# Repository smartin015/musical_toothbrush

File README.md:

```
python3 send_tones.py africa_solo_1pt.mid 1.5
```

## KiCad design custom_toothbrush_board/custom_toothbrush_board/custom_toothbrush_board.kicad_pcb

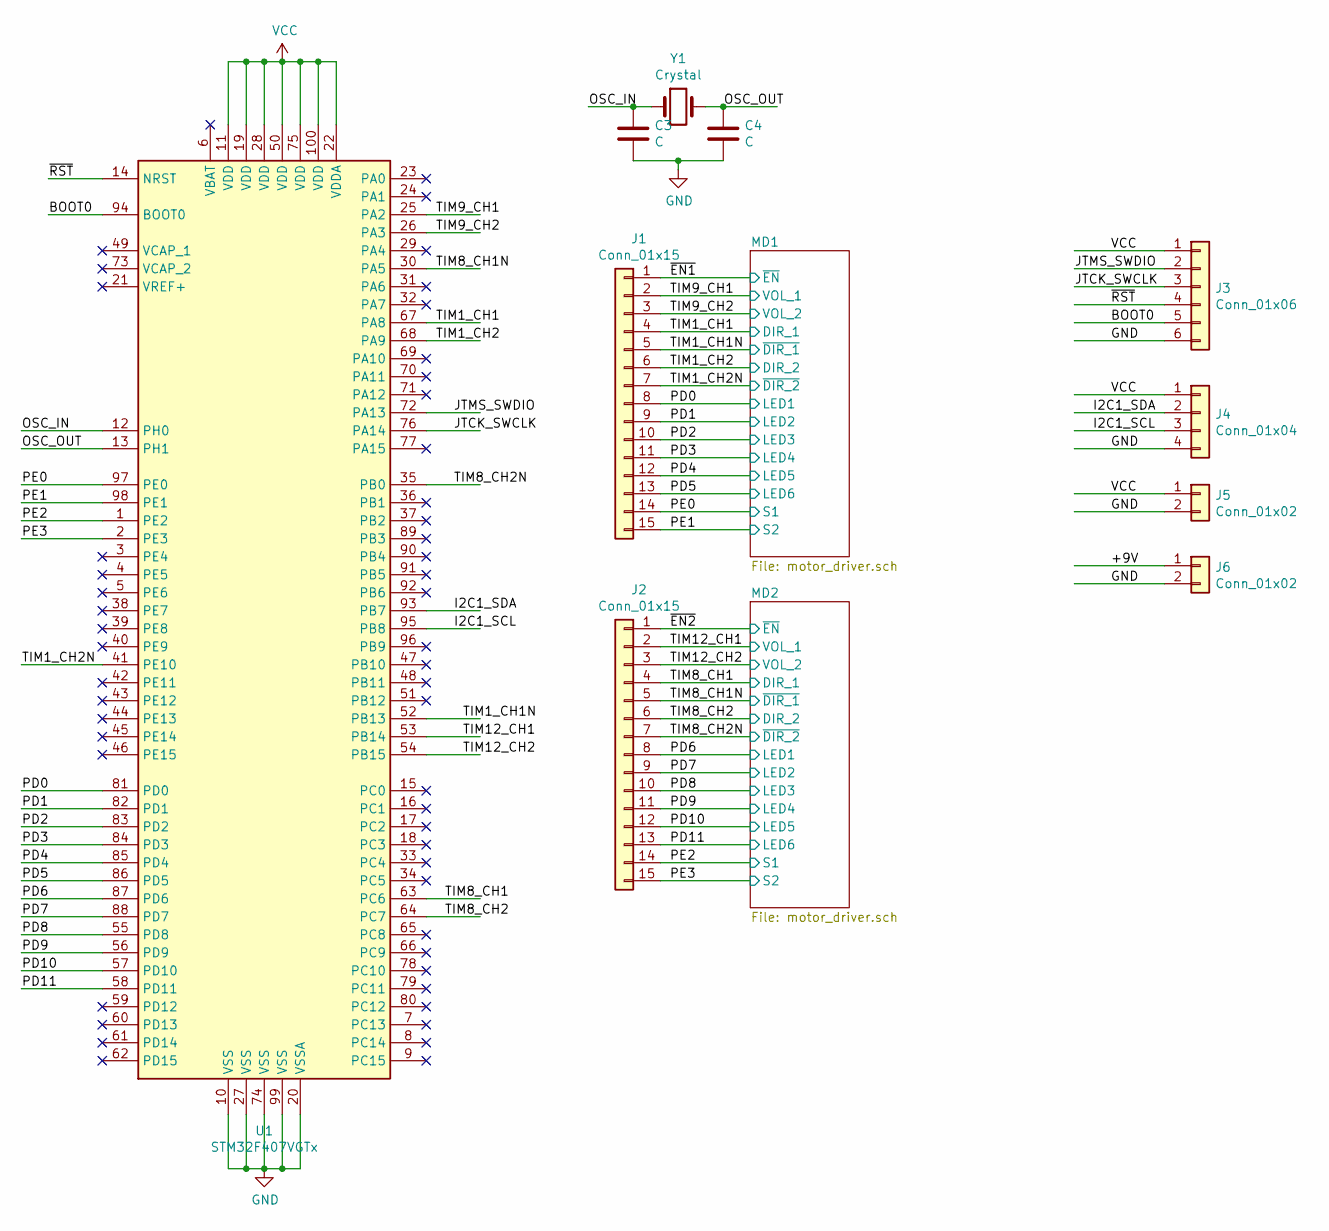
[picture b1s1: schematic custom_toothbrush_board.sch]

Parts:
C3, C4: C; C_0603_1608Metric_Pad1.08x0.95mm_HandSolder
J1, J2: Conn_01x15; PinHeader_1x15_P2.54mm_Vertical
J3: Conn_01x06; PinHeader_1x06_P2.54mm_Vertical
J4: Conn_01x04; PinHeader_1x04_P2.54mm_Vertical
J5, J6: Conn_01x02; PinHeader_1x02_P2.54mm_Vertical
U1: STM32F407VGTx; LQFP-100_14x14mm_P0.5mm
Y1: Crystal; Crystal_SMD_5032-2Pin_5.0x3.2mm_HandSoldering

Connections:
+9V: J6.1; also elsewhere on the board
/BOOT0: J3.5, U1.94 (BOOT0)
/I2C1_SCL: J4.3, U1.95 (PB8)
/I2C1_SDA: J4.2, U1.93 (PB7)
/JTCK_SWCLK: J3.3, U1.76 (PA14)
/JTMS_SWDIO: J3.2, U1.72 (PA13)
/OSC_IN: C3.1, U1.12 (PH0), Y1.1
/OSC_OUT: C4.1, U1.13 (PH1), Y1.2
/PD0: J1.8, U1.81 (PD0); also elsewhere on the board
/PD1: J1.9, U1.82 (PD1); also elsewhere on the board
/PD2: J1.10, U1.83 (PD2); also elsewhere on the board
/PD3: J1.11, U1.84 (PD3); also elsewhere on the board
/PD4: J1.12, U1.85 (PD4); also elsewhere on the board
/PD5: J1.13, U1.86 (PD5); also elsewhere on the board
/PD6: J2.8, U1.87 (PD6); also elsewhere on the board
/PD7: J2.9, U1.88 (PD7); also elsewhere on the board
/PD8: J2.10, U1.55 (PD8); also elsewhere on the board
/PD9: J2.11, U1.56 (PD9); also elsewhere on the board
/PD10: J2.12, U1.57 (PD10); also elsewhere on the board
/PD11: J2.13, U1.58 (PD11); also elsewhere on the board
/PE0: J1.14, U1.97 (PE0); also elsewhere on the board
/PE1: J1.15, U1.98 (PE1); also elsewhere on the board
/PE2: J2.14, U1.1 (PE2); also elsewhere on the board
/PE3: J2.15, U1.2 (PE3); also elsewhere on the board
/TIM1_CH1: J1.4, U1.67 (PA8); also elsewhere on the board
/TIM1_CH1N: J1.5, U1.52 (PB13); also elsewhere on the board
/TIM1_CH2: J1.6, U1.68 (PA9); also elsewhere on the board
/TIM1_CH2N: J1.7, U1.41 (PE10); also elsewhere on the board
/TIM8_CH1: J2.4, U1.63 (PC6); also elsewhere on the board
/TIM8_CH1N: J2.5, U1.30 (PA5); also elsewhere on the board
/TIM8_CH2: J2.6, U1.64 (PC7); also elsewhere on the board
/TIM8_CH2N: J2.7, U1.35 (PB0); also elsewhere on the board
/TIM9_CH1: J1.2, U1.25 (PA2); also elsewhere on the board
/TIM9_CH2: J1.3, U1.26 (PA3); also elsewhere on the board
/TIM12_CH1: J2.2, U1.53 (PB14); also elsewhere on the board
/TIM12_CH2: J2.3, U1.54 (PB15); also elsewhere on the board
/~EN1: J1.1; also elsewhere on the board
/~EN2: J2.1; also elsewhere on the board
/~RST: J3.4, U1.14 (NRST)
GND: C3.2, C4.2, J3.6, J4.4, J5.2, J6.2, U1.10 (VSS), U1.20 (VSSA), U1.27 (VSS), U1.74 (VSS), U1.99 (VSS); also elsewhere on the board
VCC: J3.1, J4.1, J5.1, U1.11 (VDD), U1.19 (VDD), U1.22 (VDDA), U1.28 (VDD), U1.50 (VDD), U1.75 (VDD), U1.100 (VDD); also elsewhere on the board

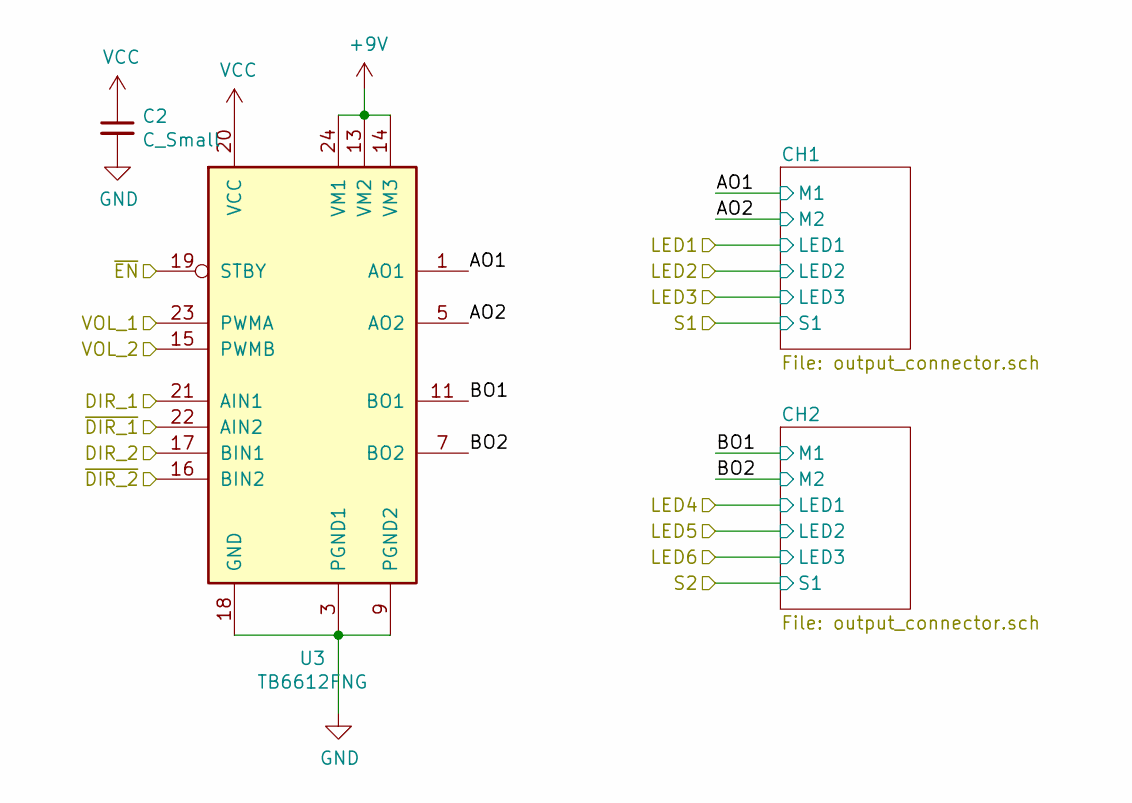
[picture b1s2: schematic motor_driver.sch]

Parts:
C1: C_Small; C_0603_1608Metric_Pad1.08x0.95mm_HandSolder
U2: TB6612FNG; SSOP-24_5.3x8.2mm_P0.65mm

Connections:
+9V: U2.13 (VM2), U2.14 (VM3), U2.24 (VM1); also elsewhere on the board
/MD1/AO1: U2.1 (AO1), U2.2 (AO1); also elsewhere on the board
/MD1/AO2: U2.5 (AO2), U2.6 (AO2); also elsewhere on the board
/MD1/BO1: U2.11 (BO1), U2.12 (BO1); also elsewhere on the board
/MD1/BO2: U2.7 (BO2), U2.8 (BO2); also elsewhere on the board
/TIM1_CH1: U2.21 (AIN1); also elsewhere on the board
/TIM1_CH1N: U2.22 (AIN2); also elsewhere on the board
/TIM1_CH2: U2.17 (BIN1); also elsewhere on the board
/TIM1_CH2N: U2.16 (BIN2); also elsewhere on the board
/TIM9_CH1: U2.23 (PWMA); also elsewhere on the board
/TIM9_CH2: U2.15 (PWMB); also elsewhere on the board
/~EN1: U2.19 (STBY); also elsewhere on the board
GND: C1.2, U2.3 (PGND1), U2.4 (PGND1), U2.9 (PGND2), U2.10 (PGND2), U2.18 (GND); also elsewhere on the board
VCC: C1.1, U2.20 (VCC); also elsewhere on the board

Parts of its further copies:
C2: C_Small; C_0603_1608Metric_Pad1.08x0.95mm_HandSolder
U3: TB6612FNG; SSOP-24_5.3x8.2mm_P0.65mm

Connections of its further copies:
+9V: U3.13 (VM2), U3.14 (VM3), U3.24 (VM1); also elsewhere on the board
/MD2/AO1: U3.1 (AO1), U3.2 (AO1); also elsewhere on the board
/MD2/AO2: U3.5 (AO2), U3.6 (AO2); also elsewhere on the board
/MD2/BO1: U3.11 (BO1), U3.12 (BO1); also elsewhere on the board
/MD2/BO2: U3.7 (BO2), U3.8 (BO2); also elsewhere on the board
/TIM8_CH1: U3.21 (AIN1); also elsewhere on the board
/TIM8_CH1N: U3.22 (AIN2); also elsewhere on the board
/TIM8_CH2: U3.17 (BIN1); also elsewhere on the board
/TIM8_CH2N: U3.16 (BIN2); also elsewhere on the board
/TIM12_CH1: U3.23 (PWMA); also elsewhere on the board
/TIM12_CH2: U3.15 (PWMB); also elsewhere on the board
/~EN2: U3.19 (STBY); also elsewhere on the board
GND: C2.2, U3.3 (PGND1), U3.4 (PGND1), U3.9 (PGND2), U3.10 (PGND2), U3.18 (GND); also elsewhere on the board
VCC: C2.1, U3.20 (VCC); also elsewhere on the board

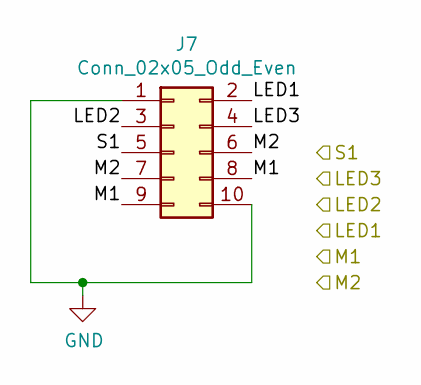
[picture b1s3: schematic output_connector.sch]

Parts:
J0: Conn_02x05_Odd_Even; 61201021621

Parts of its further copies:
J7, J8, J9, J10: Conn_02x05_Odd_Even; 61201021621

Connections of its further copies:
/MD1/AO1: J7.8, J7.9; also elsewhere on the board
/MD1/AO2: J7.6, J7.7; also elsewhere on the board
/MD1/BO1: J8.8, J8.9; also elsewhere on the board
/MD1/BO2: J8.6, J8.7; also elsewhere on the board
/MD2/AO1: J9.8, J9.9; also elsewhere on the board
/MD2/AO2: J9.6, J9.7; also elsewhere on the board
/MD2/BO1: J10.8, J10.9; also elsewhere on the board
/MD2/BO2: J10.6, J10.7; also elsewhere on the board
/PD0: J7.2; also elsewhere on the board
/PD1: J7.3; also elsewhere on the board
/PD2: J7.4; also elsewhere on the board
/PD3: J8.2; also elsewhere on the board
/PD4: J8.3; also elsewhere on the board
/PD5: J8.4; also elsewhere on the board
/PD6: J9.2; also elsewhere on the board
/PD7: J9.3; also elsewhere on the board
/PD8: J9.4; also elsewhere on the board
/PD9: J10.2; also elsewhere on the board
/PD10: J10.3; also elsewhere on the board
/PD11: J10.4; also elsewhere on the board
/PE0: J7.5; also elsewhere on the board
/PE1: J8.5; also elsewhere on the board
/PE2: J9.5; also elsewhere on the board
/PE3: J10.5; also elsewhere on the board
GND: J7.1, J7.10, J8.1, J8.10, J9.1, J9.10, J10.1, J10.10; also elsewhere on the board

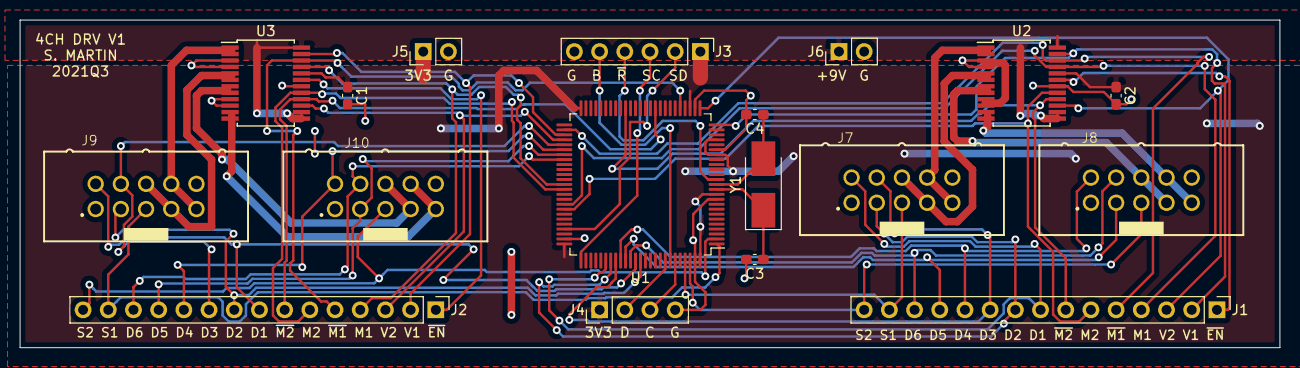
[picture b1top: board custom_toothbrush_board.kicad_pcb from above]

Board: 2 copper layers, 127.0 x 33.0 mm, 18 parts (0 on the bottom side), 49 nets.

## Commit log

2021-06-17 Successfully blessed some rains
2021-06-18 upgraded LED cycle animation, added Die Forelle midi track
2021-08-18 added custom toothbrush board (kicad)
2021-09-28 Added toothbrush mount cadquery file
